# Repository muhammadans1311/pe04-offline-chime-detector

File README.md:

# PE-04 | ESP32-S3 Offline Chime Detector

**Practical Electronics · Mechatronic Systems Engineering · Rhine-Waal University of Applied Sciences**

`ESP32-S3` · `KiCad 10` · `PCB design` · `Analog electronics` · `LTspice` · `Goertzel`

I'm working on a USB-C-powered board that listens for familiar household chimes and gives a visual indication using three LEDs. The idea is to identify the sound locally from its frequency and timing pattern rather than relying on cloud audio processing.

My part of the project has included analysing sound recordings, testing the microwave-beep detection method, working through the analog microphone circuit in LTspice and collaborating on the KiCad schematic and PCB design.

*KiCad 3D view of the 22 November 2026 V2 design. This is a computer render, not a photograph of a soldered board.*

## Project files

| | |
| --- | --- |
| **Complete schematic** | [View PDF](exports/PE04_V2_schematic.pdf) · [Editable KiCad schematic](hardware/current/PE04_Chime_Detector.kicad_sch) |
| **PCB design** | [Editable V2 PCB](hardware/current/PE04_Chime_Detector.kicad_pcb) · [PCB layout image](images/pcb/v2-pcb-layout.png) |
| **KiCad project** | [Project file, local footprints, symbols and 3D models](hardware/current/) |
| **Parts** | [V2 assembly BOM](procurement/PE04_V2_Assembly_BOM.csv) · [Supplier supplements](procurement/) |
| **Documentation** | [Circuit design](docs/hardware-architecture.md) · [PCB layout](docs/pcb-layout.md) · [LTspice](docs/ltspice-experiments.md) · [Sound analysis](docs/sound-analysis.md) |
| **Build log** | [Assembly and testing](docs/assembly-and-testing.md) |

## PCB design

| Parameter | V2 design |
| --- | --- |
| Microcontroller | ESP32-S3-WROOM-1 |
| Supply | USB-C 5 V; TLV62569 buck regulator to nominal 3.3 V |
| Audio input | AOM-5024P-HD-MB-R electret microphone |
| Analog front-end | AD8656ARZ preamplifier; TLV9062 fourth-order active low-pass |
| ADC / outputs | GPIO4 (ADC1_CH3); three independent LED channels |
| Board | 74.3 × 57.5 mm · 2 copper layers · 1.6 mm |
| Placement | 57 electronic components + four M2 mounting holes |

*The V2 layout showing the copper tracks, component placement, test points and ESP32 antenna keep-out.*

*KiCad top view. All of the files used for this render are included under `hardware/current/`.*

[PCB layout notes](docs/pcb-layout.md)

## Schematic and circuit architecture

The schematic is organized into eight blocks: USB-C, the 3.3 V buck supply, microphone bias, analog reference and preamplifier, active low-pass filter, ADC input, ESP32-S3 and the three indicators.

**Microphone → AC coupling → AD8656ARZ → TLV9062 filter → ESP32-S3 ADC → LED outputs**

[Open the full-resolution schematic PDF](exports/PE04_V2_schematic.pdf) · [See all eight circuit blocks with explanations](docs/hardware-architecture.md)

## Sound-analysis work

I analysed a microwave chime, doorbell and smoke-alarm test sound. The microwave completion tone sits close to 2,050 Hz. I first tried frequency-based detection, but hand claps caused false triggers. The next offline Python version used a Goertzel tone check, tone-purity threshold and three-beep timing rule.

The four development recordings gave alert counts of **1, 1, 1 and 0**, matching the expected counts for the two microwave recordings, the microwave-with-claps recording and the clap-only recording. This was an offline test on four files, not a measured accuracy rate for the finished device. Doorbell and smoke-alarm recognition still need separate detection rules.

[Read the sound-analysis notes](docs/sound-analysis.md)

## LTspice experiments

I used LTspice to explore microphone biasing, the 1.65 V analog reference, preamplifier gain, filtering and transient behaviour. I also investigated a supplier op-amp model that had convergence issues in a multi-stage circuit.

The saved early amplifier-plus-RC-filter simulation reads **+20.08 dB at 2.054 kHz** for `V(adc_out)/V(mic_raw)`. This plot belongs to that development circuit; it is not a measurement or complete simulation of the current AD8656ARZ/TLV9062 board.

[View the original LTspice screenshots and notes](docs/ltspice-experiments.md)

## Build status

| Work | Status |
| --- | --- |
| V2 KiCad schematic, PCB and local libraries | Available |
| V2 schematic PDF, PCB layout and 3D views | Available |
| Parts list and assembly BOM | Available |
| Microwave detection experiments | Offline tests documented |
| LTspice front-end experiments | Screenshots documented |
| KiCad ERC/DRC results | Not recorded in this repository |
| Board soldering and first power-up | Pending |
| ESP32 firmware and on-board sound recognition | Pending |

After assembly we'll add board photographs, power measurements, analog test waveforms and the actual firmware results to the [build log](docs/assembly-and-testing.md).

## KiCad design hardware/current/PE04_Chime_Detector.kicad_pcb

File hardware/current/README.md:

# PE-04 V2 KiCad source

This folder contains the project files supplied for the current team design revision, dated **22 November 2026** (V2). The files have not been altered during GitHub packaging.

Open **`PE04_Chime_Detector.kicad_pro`** in KiCad 10. Keep the `libraries/` folder, `fp-lib-table` and `sym-lib-table` alongside the project. The footprint and symbol tables use paths relative to `${KIPRJMOD}`. Custom `.kicad_mod`, `.kicad_sym` and STEP 3D files are included.

The `.kicad_prl` (local preferences/session state), macOS metadata and `.DS_Store` were intentionally omitted.

- `PE04_Chime_Detector.kicad_sch`: V2 schematic
- `PE04_Chime_Detector.kicad_pcb`: V2 two-layer PCB
- `PE04_Chime_Detector.kicad_pro`: matching project settings
- `PE04_Chime_Detector.kicad_dru`: supplied AISLER-based design rules
- `fp-lib-table` and `sym-lib-table`: project libraries
- `libraries/`: custom footprints, symbols and 3D models

There are 57 electronic components and four mounting holes in the PCB file. Design rules are supplied, but no passing KiCad ERC or DRC report was provided. The next steps are review, assembly and bench tests.

Earlier native files are preserved in [hardware/archive/earlier-kicad-sources](../archive/earlier-kicad-sources/) for development history.

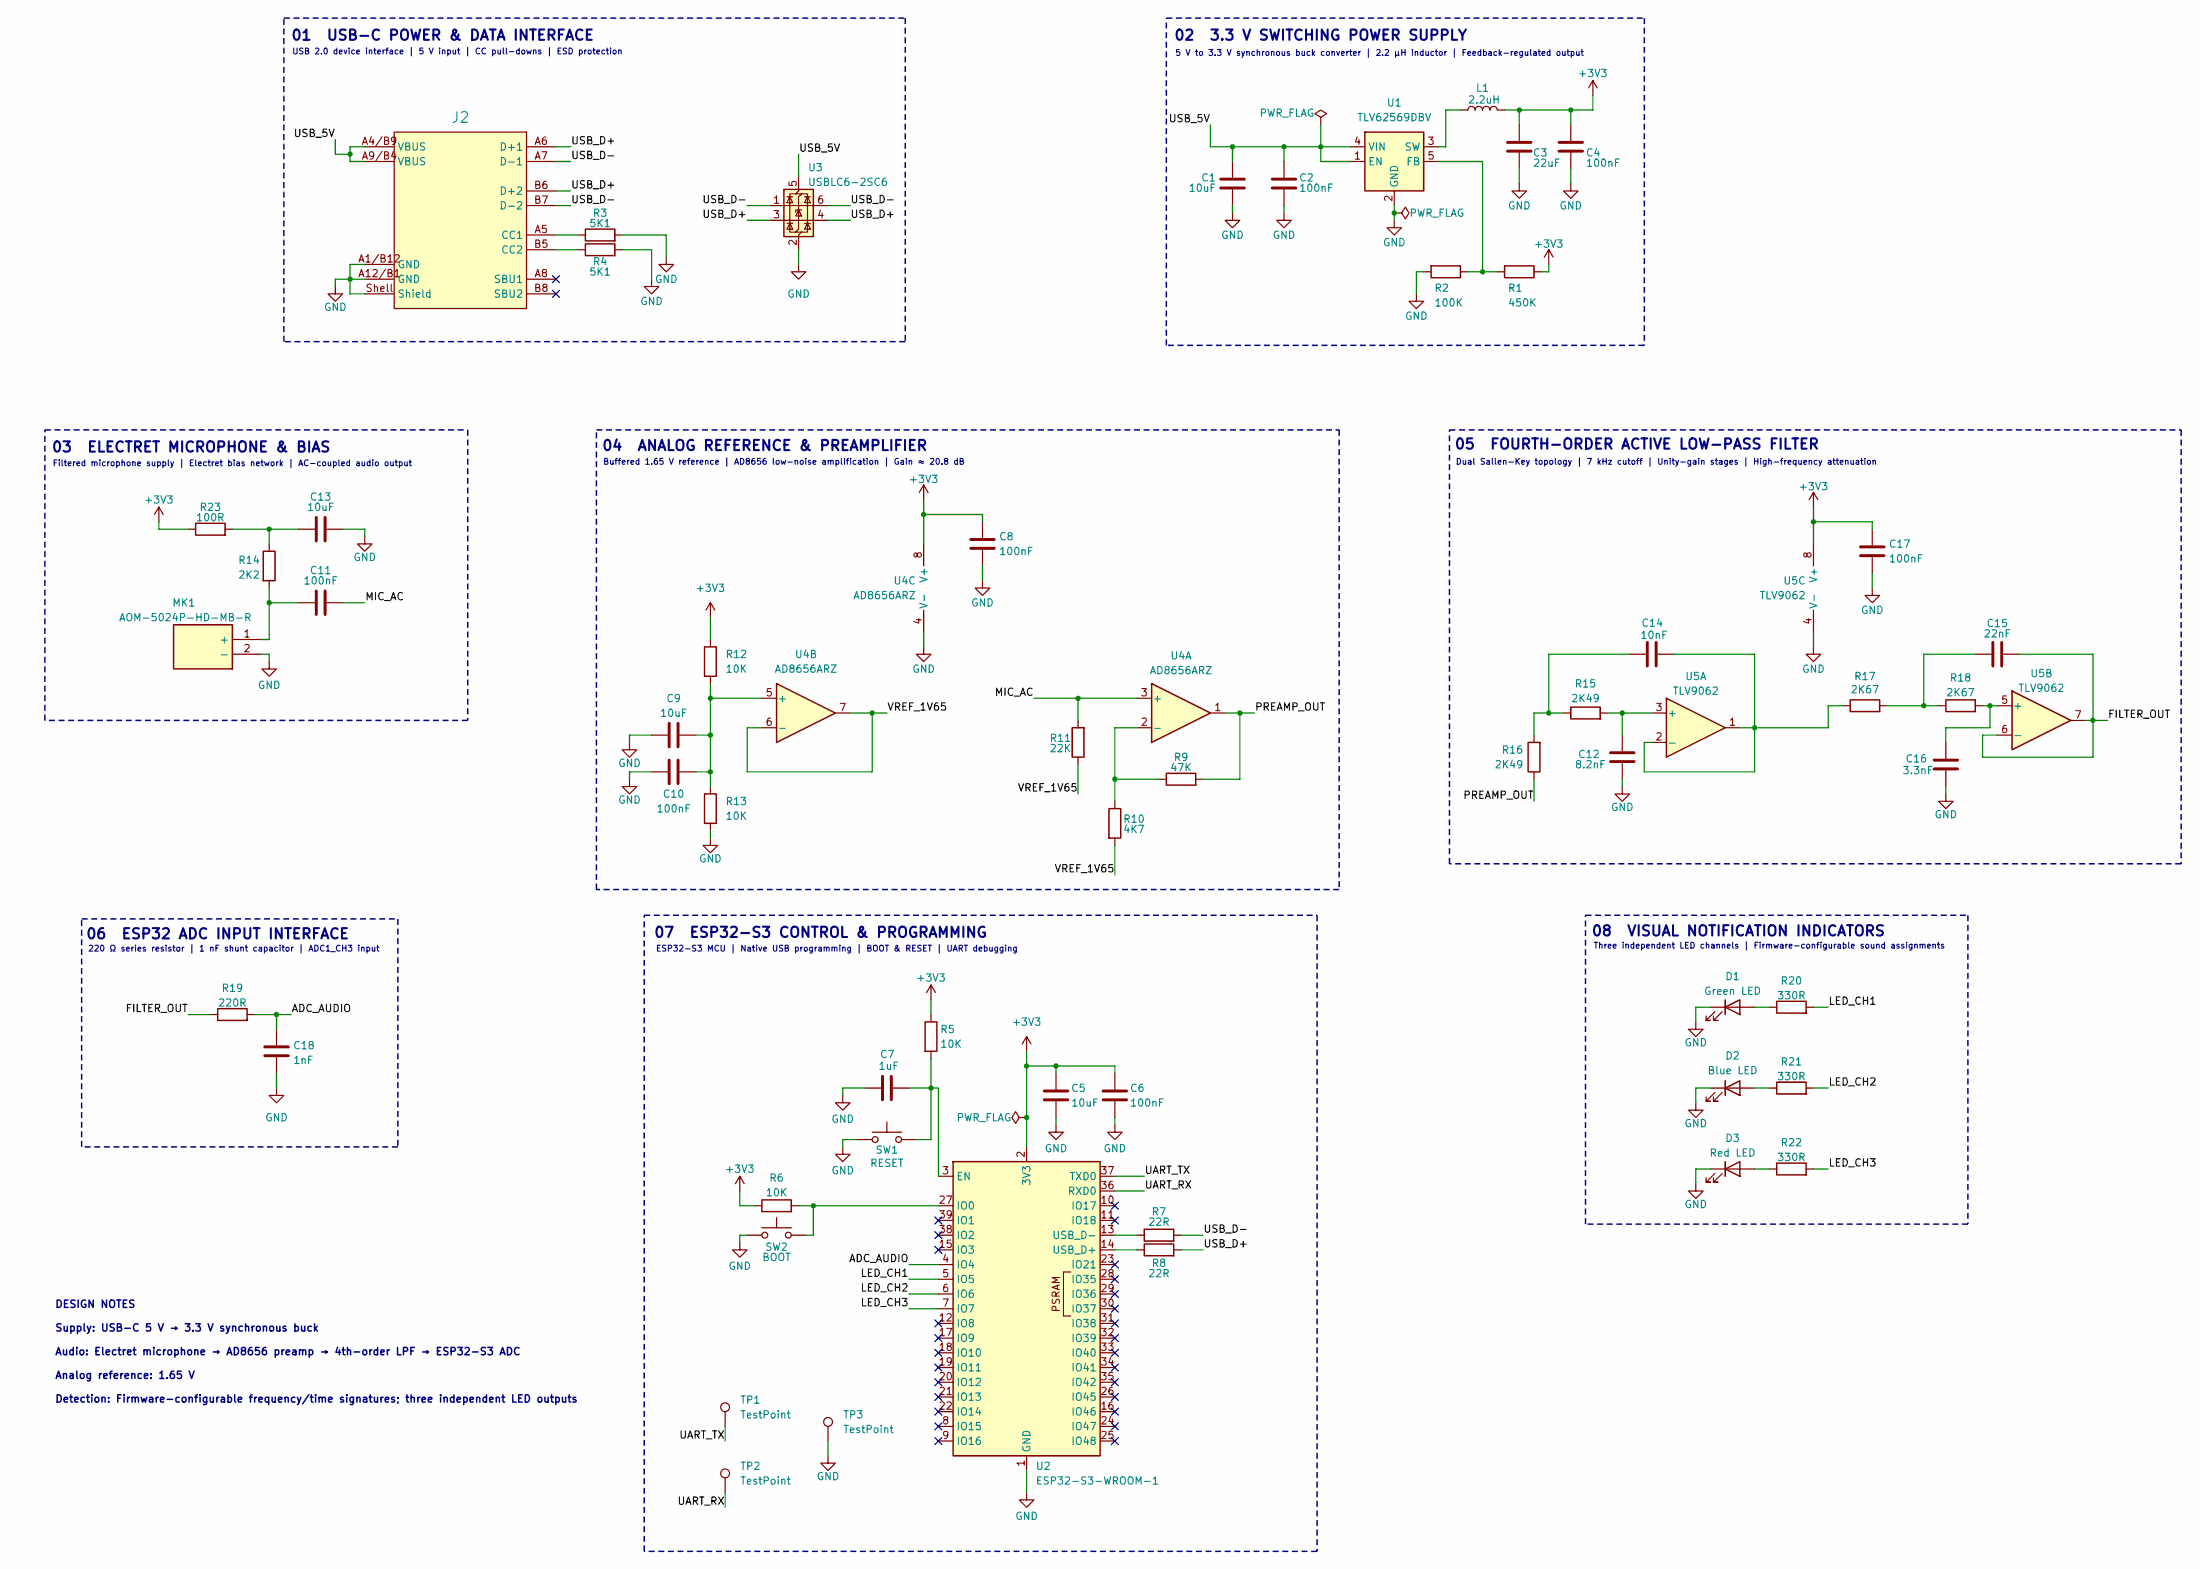
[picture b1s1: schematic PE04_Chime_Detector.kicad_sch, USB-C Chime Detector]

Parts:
C1, C5, C9, C13: 10uF; C_1206_3216Metric_Pad1.33x1.80mm_HandSolder
C2, C8, C10, C11, C17: 100nF; C_0805_2012Metric_Pad1.18x1.45mm_HandSolder
C3: 22uF; C_1206_3216Metric_Pad1.33x1.80mm_HandSolder; MPN GRM31CR71A226KE15L
C4, C6: 100nF; C_0805_2012Metric_Pad1.18x1.45mm_HandSolder_Variant2
C7: 1uF; C_0805_2012Metric_Pad1.18x1.45mm_HandSolder_Variant2
C12: 8.2nF; C_0805_2012Metric_Pad1.18x1.45mm_HandSolder_Variant2
C14: 10nF; C_0805_2012Metric_Pad1.18x1.45mm_HandSolder
C15: 22nF; C_0805_2012Metric_Pad1.18x1.45mm_HandSolder
C16: 3.3nF; C_0805_2012Metric_Pad1.18x1.45mm_HandSolder
C18: 1nF; C_0805_2012Metric_Pad1.18x1.45mm_HandSolder_Variant2
D1: Green LED; LED_1206_3216Metric
D2: Blue LED; LED_1206_3216Metric
D3: Red LED; LED_1206_3216Metric
J2: 629722000214; USB_C_629722000214_AISLER; Working Voltage 48V (DC); Manufacturer Part Number 629722000214
L1: 2.2uH; L_Taiyo-Yuden_NR-40xx_HandSoldering; MPN LSXND4040TKL2R2MDG
MK1: AOM-5024P-HD-MB-R; AOM5024PHDMBR; Manufacturer_Part_Number AOM-5024P-HD-MB-R; Mouser Part Number 665-AOM5024P-HD-MB-R
R1: 450K; R_0805_2012Metric_Pad1.20x1.40mm_HandSolder
R2: 100K; R_0805_2012Metric_Pad1.20x1.40mm_HandSolder_Variant2
R3: 5K1; R_0805_2012Metric_Pad1.20x1.40mm_HandSolder_Variant2
R4: 5K1; R_0805_2012Metric_Pad1.20x1.40mm_HandSolder
R5: 10K; R_0805_2012Metric_Pad1.20x1.40mm_HandSolder_Variant2
R6, R12, R13: 10K; R_0805_2012Metric_Pad1.20x1.40mm_HandSolder
R7, R8: 22R; R_0805_2012Metric_Pad1.20x1.40mm_HandSolder
R9: 47K; R_0805_2012Metric_Pad1.20x1.40mm_HandSolder_Variant2
R10: 4K7; R_0805_2012Metric_Pad1.20x1.40mm_HandSolder_Variant2
R11: 22K; R_0805_2012Metric_Pad1.20x1.40mm_HandSolder
R14: 2K2; R_0805_2012Metric_Pad1.20x1.40mm_HandSolder
R15, R16: 2K49; R_0805_2012Metric_Pad1.20x1.40mm_HandSolder_Variant2
R17: 2K67; R_0805_2012Metric_Pad1.20x1.40mm_HandSolder
R18: 2K67; R_0805_2012Metric_Pad1.20x1.40mm_HandSolder_Variant2
R19: 220R; R_0805_2012Metric_Pad1.20x1.40mm_HandSolder_Variant2
R20, R21, R22: 330R; R_0805_2012Metric_Pad1.20x1.40mm_HandSolder_Variant2
R23: 100R; R_0805_2012Metric_Pad1.20x1.40mm_HandSolder_Variant2
SW1: RESET; SW_PUSH_6mm
SW2: BOOT; SW_PUSH_6mm
TP1, TP2, TP3: TestPoint; TestPoint_Pad_D2.0mm
U1: TLV62569DBV; SOT-23-5
U2: ESP32-S3-WROOM-1; ESP32-S3-WROOM-1_AISLER
U3: USBLC6-2SC6; SOT-23-6
U4: AD8656ARZ; SOIC-8_3.9x4.9mm_P1.27mm
U5: TLV9062; SOIC-8_3.9x4.9mm_P1.27mm_Variant2

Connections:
+3V3: C3.1, C4.1, C5.1, C6.1, C8.1, C17.1, L1.1, R1.1, R5.1, R6.1, R12.1, R23.1, U2.2 (3V3), U4.8 (V+), U5.8 (V+)
/ADC_AUDIO: C18.1, R19.2, U2.4 (IO4)
/FILTER_OUT: C15.2, R19.1, U5.6 (-), U5.7
/LED_CH1: R20.2, U2.5 (IO5)
/LED_CH2: R21.2, U2.6 (IO6)
/LED_CH3: R22.2, U2.7 (IO7)
/MIC_AC: C11.1, R11.2, U4.3 (+)
/PREAMP_OUT: R9.2, R16.1, U4.1
/UART_RX: TP2.1 (1_1), U2.36 (RXD0)
/UART_TX: TP1.1 (1_1), U2.37 (TXD0)
/USB_5V: C1.1, C2.1, J2.A4/B9 (VBUS), J2.A9/B4 (VBUS), U1.1 (EN), U1.4 (VIN), U3.5 (VBUS)
/USB_D+: J2.A6 (D+1), J2.B6 (D+2), R8.2, U3.3 (I/O2), U3.4 (I/O2)
/USB_D-: J2.A7 (D-1), J2.B7 (D-2), R7.2, U3.1 (I/O1), U3.6 (I/O1)
/VREF_1V65: R10.2, R11.1, U4.6 (-), U4.7
GND: C1.2, C2.2, C3.2, C4.2, C5.2, C6.2, C7.2, C8.2, C9.1, C10.2, C12.2, C13.1, C16.1, C17.2, C18.2, D1.1 (K), D2.1 (K), D3.1 (K), J2.A1/B12 (GND), J2.A12/B1 (GND), J2.Shell (Shield), MK1.2 (-), R2.2, R3.2, R4.2, R13.2, SW1.1, SW2.1, TP3.1 (1_1), U1.2 (GND), U2.1 (GND), U2.40 (GND), U2.41 (GND), U3.2 (GND), U4.4 (V-), U5.4 (V-)
unnamed: C13.2, R14.1, R23.2
unnamed: C14.1, R15.1, R16.2
unnamed: C15.1, R17.2, R18.1
unnamed: D1.2 (A), R20.1
unnamed: D2.2 (A), R21.1
unnamed: D3.2 (A), R22.1
unnamed: J2.A5 (CC1), R3.1
unnamed: J2.B5 (CC2), R4.1
unnamed: C11.2, MK1.1 (+), R14.2
unnamed: R1.2, R2.1, U1.5 (FB)
unnamed: L1.2, U1.3 (SW)
unnamed: C7.1, R5.2, SW1.2, U2.3 (EN)
unnamed: R6.2, SW2.2, U2.27 (IO0)
unnamed: R8.1, U2.14 (USB_D+)
unnamed: R7.1, U2.13 (USB_D-)
unnamed: R9.1, R10.1, U4.2 (-)
unnamed: C9.2, C10.1, R12.2, R13.1, U4.5 (+)
unnamed: C12.1, R15.2, U5.3 (+)
unnamed: C14.2, R17.1, U5.1, U5.2 (-)
unnamed: C16.2, R18.2, U5.5 (+)

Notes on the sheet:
DESIGN NOTES Supply: USB-C 5 V → 3.3 V synchronous buck Audio: Electret microphone → AD8656 preamp → 4th-order LPF → ESP32-S3 ADC Analog reference: 1.65 V Detection: Firmware-configurable frequency/time signatures; three independent LED outputs
Filtered microphone supply | Electret bias network | AC-coupled audio output
07 ESP32-S3 CONTROL & PROGRAMMING
220 Ω series resistor | 1 nF shunt capacitor | ADC1_CH3 input
5 V to 3.3 V synchronous buck converter | 2.2 µH inductor | Feedback-regulated output
Three independent LED channels | Firmware-configurable sound assignments
USB 2.0 device interface | 5 V input | CC pull-downs | ESD protection
01 USB-C POWER & DATA INTERFACE
03 ELECTRET MICROPHONE & BIAS
ESP32-S3 MCU | Native USB programming | BOOT & RESET | UART debugging
04 ANALOG REFERENCE & PREAMPLIFIER
06 ESP32 ADC INPUT INTERFACE
Dual Sallen-Key topology | 7 kHz cutoff | Unity-gain stages | High-frequency attenuation
02 3.3 V SWITCHING POWER SUPPLY
Buffered 1.65 V reference | AD8656 low-noise amplification | Gain ≈ 20.8 dB
08 VISUAL NOTIFICATION INDICATORS
05 FOURTH-ORDER ACTIVE LOW-PASS FILTER

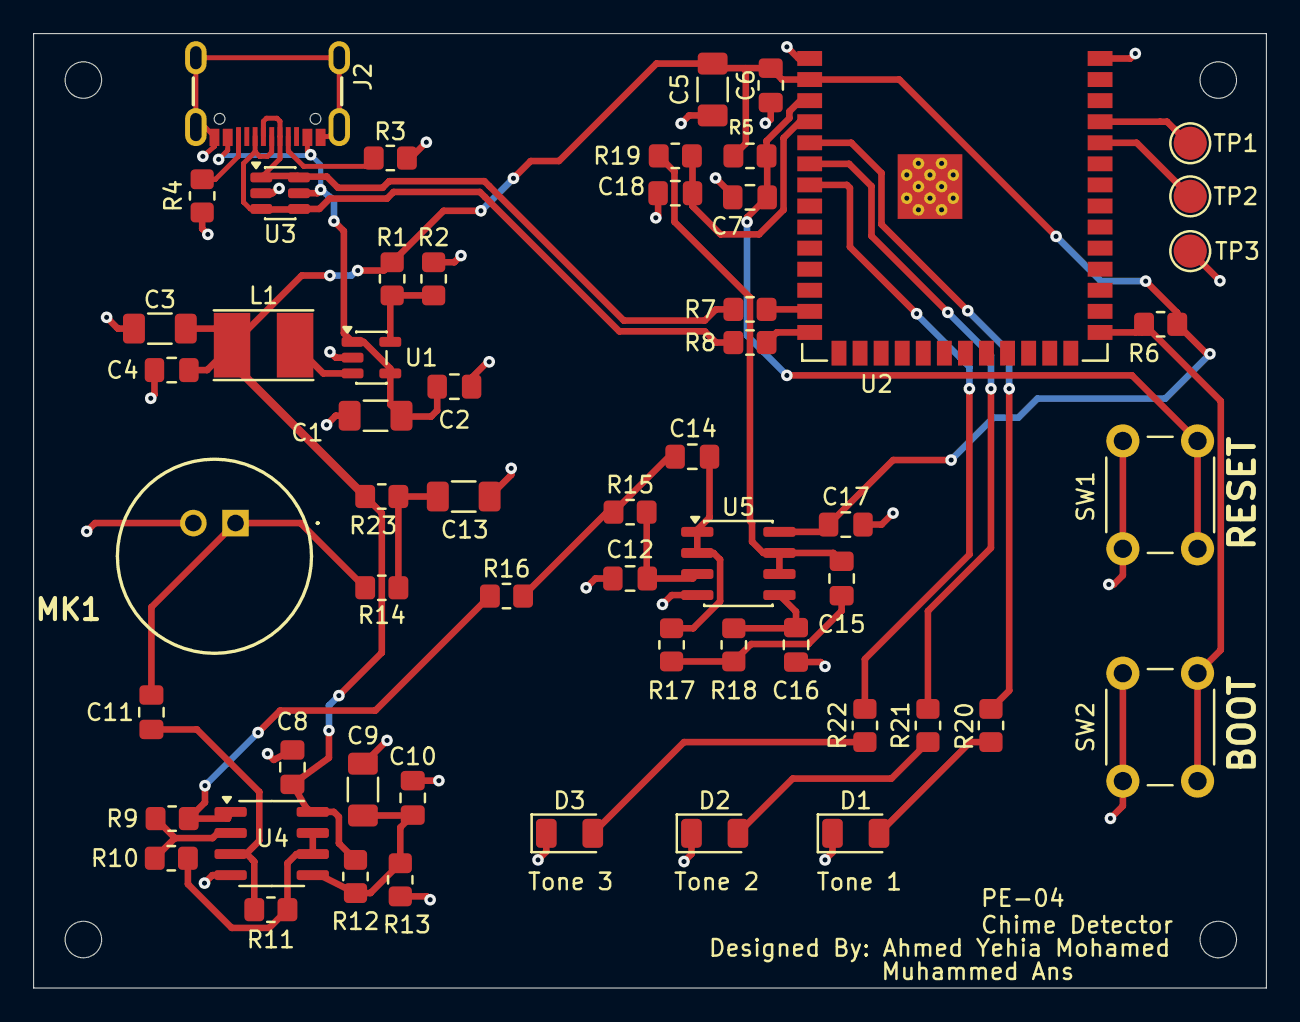
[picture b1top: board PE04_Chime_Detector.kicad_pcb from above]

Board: 2 copper layers, 74.3 x 57.5 mm, 61 parts (0 on the bottom side), 35 nets.

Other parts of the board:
H1, H2, H3, H4: MountingHole_2.2mm_M2

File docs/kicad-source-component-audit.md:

# KiCad component source audit — archived native revision

> **Source-of-truth scope:** This audit compares the **actual two native design files currently archived in this repository**, not the later November 18 layout screenshot. The screenshot's matching editable PCB is not yet available. These are design-file values, **not a validated assembled BOM**.

## Sources used

- [Archived KiCad schematic](../hardware/archive/earlier-kicad-sources/PraticalElectronics_AY2.kicad_pro%281%29.kicad_sch) (`.kicad_sch`, KiCad 10)
- [Archived KiCad PCB](../hardware/archive/earlier-kicad-sources/PE04_Chime_Detector_Schematics.kicad_pcb) (`.kicad_pcb`, KiCad 10)
- [Eight-block circuit guide](../reports/eight-block-circuit-guide.pdf) (secondary explanatory reference)

## Result

- **57 physical PCB footprints** identified.
- **57 unique non-power physical schematic references** identified (multi-unit op-amps U4/U5 counted once).
- **0 reference/value mismatches** between physical PCB and archived schematic.
- **0 schematic physical references missing from PCB**.
- This compares **reference designators and Value fields only**. It does **not** verify electrical connectivity, pin nets, footprints-to-symbol pin maps, actual purchased parts, ERC, DRC, or the newer screenshot.

## Important design values

| Function | Native reference(s) | Value or part |
| --- | --- | --- |
| USB-C receptacle | J2 | 629722000214 |
| USB-C CC pull-downs | R3, R4 | 5K1 each |
| USB data protection | U3 | USBLC6-2SC6 |
| 3.3 V buck regulator | U1 | TLV62569DBV |
| Feedback network | R1, R2 | 450K, 100K |
| Buck inductor | L1 | 2.2uH |
| Controller | U2 | ESP32-S3-WROOM-1 |
| Microphone | MK1 | AOM-5024P-HD-MB-R |
| Microphone bias / decoupling | R14, R23, C13, C11 | 2K2, 100R, 10uF, 100nF |
| Midrail reference | R12, R13 | 10K each (nominal 1.65 V from 3.3 V) |
| Analog preamp | U4 | AD8656, with R9=47K and R10=4K7 (nominal 11×) |
| Active filter | U5 | TLV9062, two Sallen–Key sections, nominal target near 7 kHz **per design documentation** |
| First filter stage | R15, R16, C12, C14 | 2K49, 2K49, 8.2nF, 10nF |
| Second filter stage | R17, R18, C15, C16 | 2K67, 2K67, 22nF, 3.3nF |
| ADC input | R19, C18 | 220R, 1nF |
| LED channels | D1, D2, D3; R20, R21, R22 | Green, blue, red; 330R each |
| Debugging | SW1, SW2, TP1, TP2, TP3 | RESET, BOOT, three test points |

**Clarification:** Earlier LTspice experiments used generic op amps and an MCP6021-family model. **Neither MCP6021 nor UniversalOpamp2 appears as a final amplifier value in these archived KiCad design files.** Their simulations are **earlier alternatives**, not simulations of this AD8656/TLV9062 PCB. Another earlier microphone candidate AOM-5024L-HD-R is **not** the MK1 part currently saved in this design.

## All 57 physical components, checked by reference and value

| Reference | PCB Value | Schematic Value | Comparison |
| --- | --- | --- | --- |
| C1 | 10uF | 10uF | Matches |
| C2 | 100nF | 100nF | Matches |
| C3 | 22uF | 22uF | Matches |
| C4 | 100nF | 100nF | Matches |
| C5 | 10uF | 10uF | Matches |
| C6 | 100nF | 100nF | Matches |
| C7 | 1uF | 1uF | Matches |
| C8 | 100nF | 100nF | Matches |
| C9 | 10uF | 10uF | Matches |
| C10 | 100nF | 100nF | Matches |
| C11 | 100nF | 100nF | Matches |
| C12 | 8.2nF | 8.2nF | Matches |
| C13 | 10uF | 10uF | Matches |
| C14 | 10nF | 10nF | Matches |
| C15 | 22nF | 22nF | Matches |
| C16 | 3.3nF | 3.3nF | Matches |
| C17 | 100nF | 100nF | Matches |
| C18 | 1nF | 1nF | Matches |
| D1 | Green LED | Green LED | Matches |
| D2 | Blue LED | Blue LED | Matches |
| D3 | Red LED | Red LED | Matches |
| J2 | 629722000214 | 629722000214 | Matches |
| L1 | 2.2uH | 2.2uH | Matches |
| MK1 | AOM-5024P-HD-MB-R | AOM-5024P-HD-MB-R | Matches |
| R1 | 450K | 450K | Matches |
| R2 | 100K | 100K | Matches |
| R3 | 5K1 | 5K1 | Matches |
| R4 | 5K1 | 5K1 | Matches |
| R5 | 10K | 10K | Matches |
| R6 | 10K | 10K | Matches |
| R7 | 22R | 22R | Matches |
| R8 | 22R | 22R | Matches |
| R9 | 47K | 47K | Matches |
| R10 | 4K7 | 4K7 | Matches |
| R11 | 22K | 22K | Matches |
| R12 | 10K | 10K | Matches |
| R13 | 10K | 10K | Matches |
| R14 | 2K2 | 2K2 | Matches |
| R15 | 2K49 | 2K49 | Matches |
| R16 | 2K49 | 2K49 | Matches |
| R17 | 2K67 | 2K67 | Matches |
| R18 | 2K67 | 2K67 | Matches |
| R19 | 220R | 220R | Matches |
| R20 | 330R | 330R | Matches |
| R21 | 330R | 330R | Matches |
| R22 | 330R | 330R | Matches |
| R23 | 100R | 100R | Matches |
| SW1 | RESET | RESET | Matches |
| SW2 | BOOT | BOOT | Matches |
| TP1 | TestPoint | TestPoint | Matches |
| TP2 | TestPoint | TestPoint | Matches |
| TP3 | TestPoint | TestPoint | Matches |
| U1 | TLV62569DBV | TLV62569DBV | Matches |
| U2 | ESP32-S3-WROOM-1 | ESP32-S3-WROOM-1 | Matches |
| U3 | USBLC6-2SC6 | USBLC6-2SC6 | Matches |
| U4 | AD8656 | AD8656 | Matches |
| U5 | TLV9062 | TLV9062 | Matches |

## Validation still required

1. Obtain the **matching native files for the latest screenshot** and rerun this audit on that exact version.
2. Run native KiCad ERC and DRC and review warnings and unconnected pad declarations.
3. Check actual nets, USB-C, converter feedback, analog reference/filter topology, footprint mapping and supply-current requirements with datasheets.
4. Only then export a production BOM and manufacturing files.
